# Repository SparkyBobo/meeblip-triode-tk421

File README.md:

# That Time I Promised My Friend a Synth… and Finally Delivered (40 Years Later!)

Let’s rewind to the 1980s—big hair, neon everything, and me, a seventh grader with a wild electronics obsession. Enter my buddy “F” (not his real name, but let’s roll with it—think F Murray Abraham from Amadeus,

because inside jokes are forever). F was the piano prodigy, I was the kid who thought soldering irons were cool, and together we were the ultimate middle school odd couple.

One day, I had a brilliant idea: “Hey F, why don’t you give me a few hundred bucks so I can build you a Moog-style synthesizer from a magazine article?” Because that’s how open-source worked back then—no GitHub, just guts and glue.

F, being the wise soul, realized this was probably a recipe for disaster (and possibly a fire hazard). Instead, F asked for a Roland synth for Christmas. Smart move, right? That was the moment F’s musical journey truly began.

He’s now a fantastic musician, and we rocked out in our high school band, the *Residudes*. F swears my synth hype is what nudged him from classical piano to modern music, so I’ll take partial credit for his rockstar status.

Fast forward: F and I still swap music nerd tidbits. He’s even inspired me to learn music (shoutout to my 70+ day Duolingo streak!). But here’s the kicker—I never actually built that synth. Oops. So, I decided it was time to

make good on my decades-old promise. After some deep dives into my parts bin and the wilds of the internet, I found the perfect open-source project: the [MeeBlip Triode](https://meeblip.com/products/meeblip-triode-synthesizer). It’s affordable, it’s awesome, and it’s my way of finally delivering on that synth promise from the Reagan era.

So here’s to friendship, music, and never letting a 40-year-old promise die. Sometimes, the best things really are worth the wait.

## Build Notes: AKA “How I Frankensteined This Synth Together”

* Parts Bin Olympics: My main goal was to spend as little money as possible on parts, not to be cheap, just to makes this a thing I threw together as much as possible.
* Analog Chip Hunt: Turns out, my stash didn’t have the right analog chips. Had to buy those. Same story for eight matching 10k potentiometers—those got ordered, but I did have a vintage audio taper 10k for volume just chilling in the bin.
* Processor Swap: The original build called for a different processor, but I had an ATMega 644 lying around, so why not? Plus, the DIP-40 package gives it that retro “I built this in the 80s” vibe. I tried to stick to the original circuit and microprocessor connections as much as possible not because I'm afraid of firmware changes, I just thoughts it would be easier.
* Through-Hole Throwback: Most resistors and capacitors are through-hole, because that’s what I had and they look delightfully vintage. Non-electrolytic caps? All from a random kit I bought for experimenting.
* Why use 1 part when 2 will do: Some components ended up with two passives in parallel or series. Why? Because I was determined to use what I had instead of buying new stuff. If you spot C14.1, C14.2, R15.1, or R15.2 looking a little extra, that’s just me flexing my parts bin muscles.
* Surface Mount Sneak-In: A few surface mount parts made it in, mostly to save space and because I had leftovers. Sorry for the modern touch, but hey, it’s all about balance.
* PCB Front Panel Hack: I love using PCBs as front panels—Kicad makes layout a breeze and it’s cheap. This synth is rocking three boards: bottom for the guts, middle for perfect potentiometer height, and the faceplate for that pro finish.
* Oldest Part Award: The power switch is a true relic—I’ve been lugging it around since the late 80s. It's actually an ON-OFF-ON switch but I thought when else am I gonna use it? And what's so bad about having 2 on positions? Runnerup is the resistors: Straight outta my college electronics kit from the late 80s/early 90s.

## Where Credit Is Due

Let’s be real: this project is standing on the shoulders of other. I didn’t just whip up the MeeBlip Triode out of thin air—there’s a whole crew who did the heavy lifting long before I ever busted out my soldering iron. So, here’s a big, sparkly shout-out (because it’s not just what the license says, it’s the right thing to do):

MeeBlip Contributors:

* Jarek Ziembicki: The OG—created the original AVRsynth, which is the backbone of this whole project.
* Laurie Biddulph: Translation superstar! Worked with Jarek to make those comments readable in English and ported the code to Atmega16.
* Daniel Kruszyna: Idea machine—extended AVRsynth and sprinkled in several concepts that MeeBlip now rocks.
* Julian Schmidt: Filter genius—came up with the original Meeblip digital filter algorithm.
* Axel Werner: Code ninja—optimized, squashed bugs, and brought in new bandlimited waveforms.
* James Grahame: Hardware and firmware mastermind behind MeeBlip’s physical and digital awesomeness.
* [MeeBlip Triode on GitHub](https://github.com/MeeBlip/meeblip-triode)

So, if you’re loving this synth saga, send some good vibes to these legends. Without their brainpower, my 40-year-old promise would still be stuck in the parts bin!

Sparky: 

F:

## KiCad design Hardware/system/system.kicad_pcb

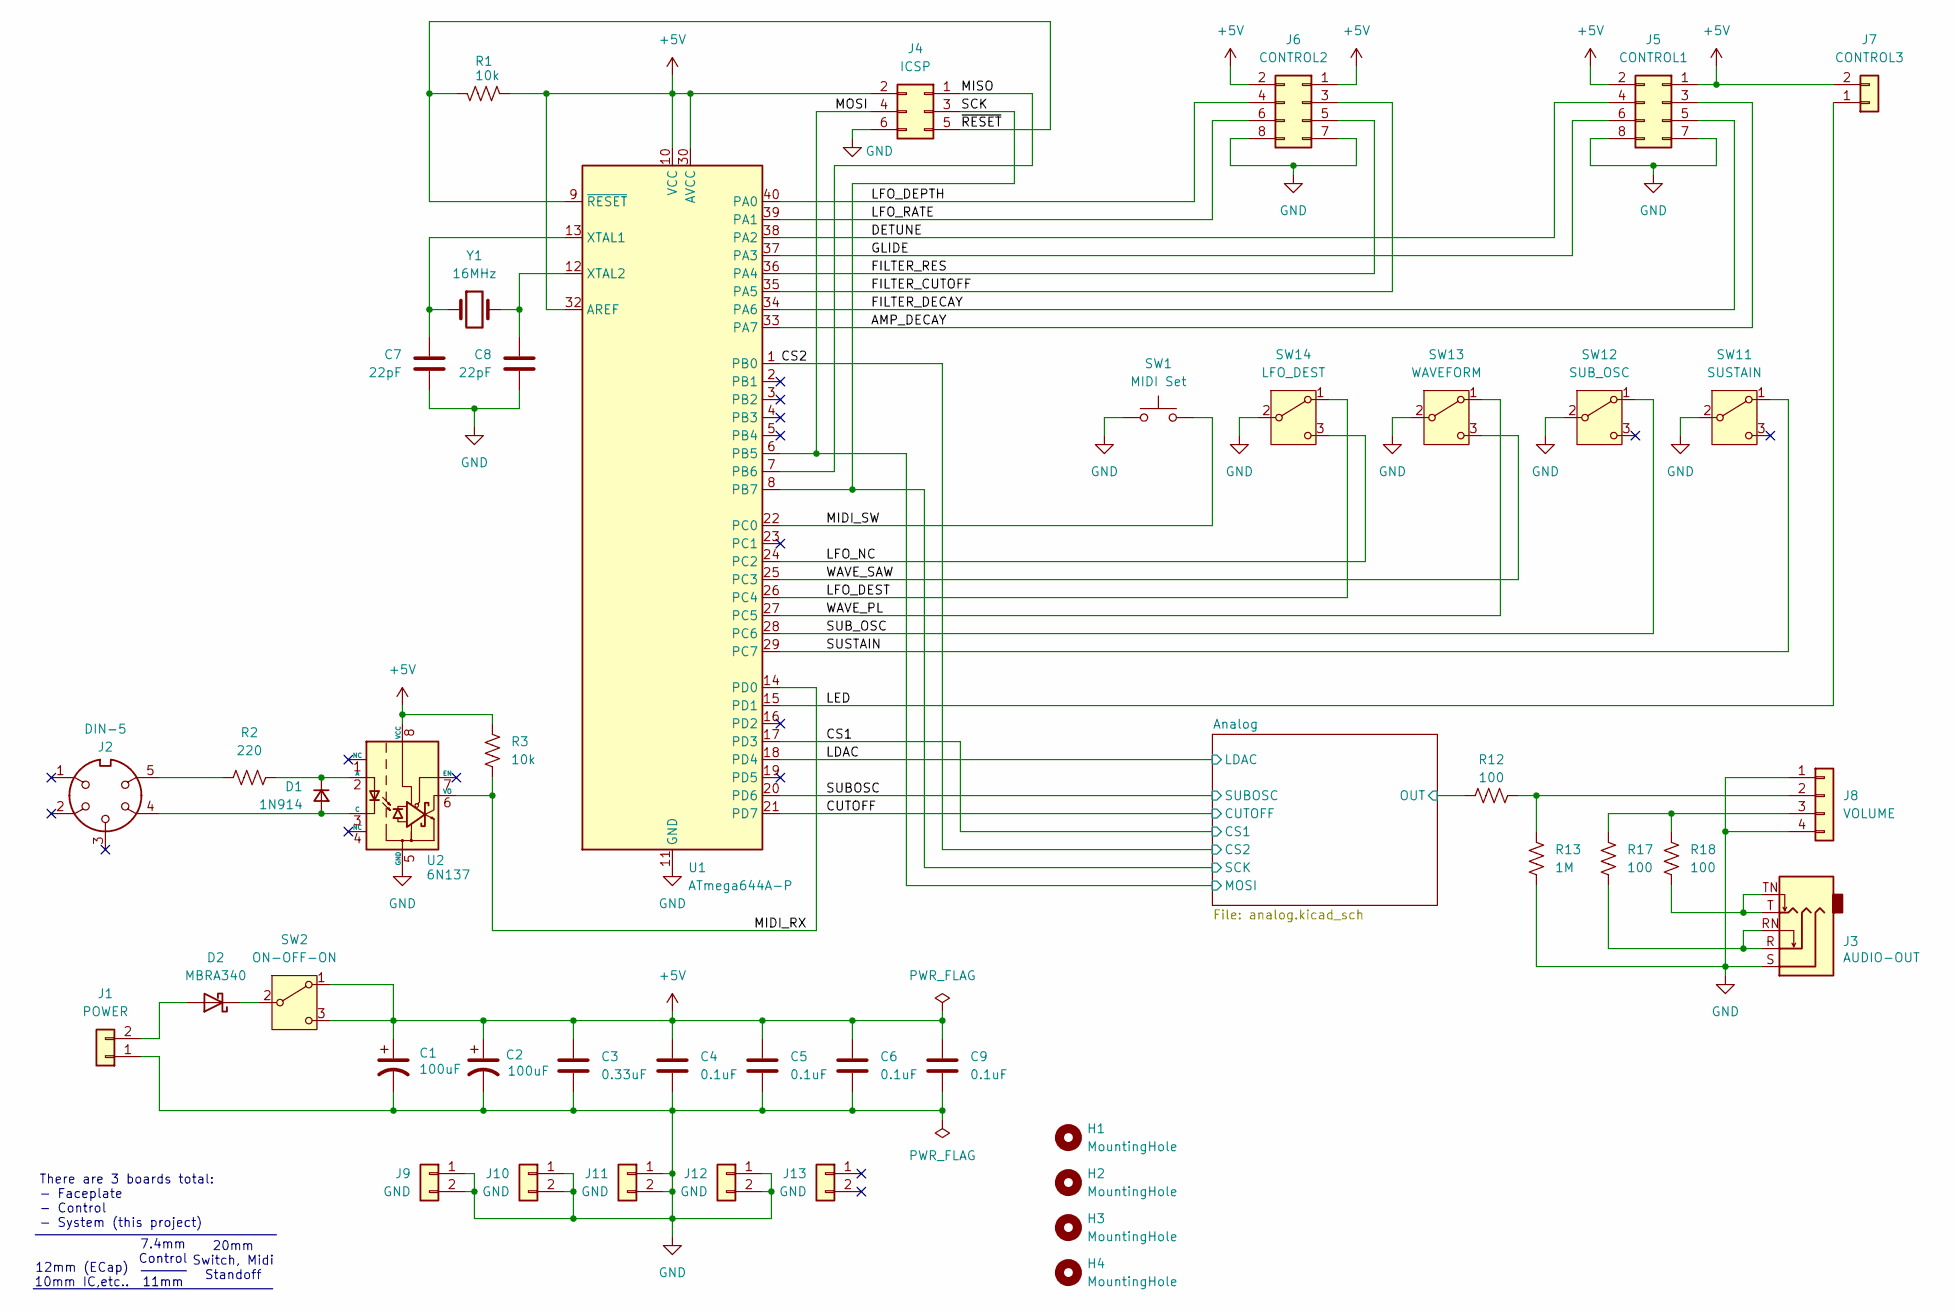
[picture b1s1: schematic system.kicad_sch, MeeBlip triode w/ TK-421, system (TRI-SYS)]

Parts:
C1, C2: 100uF; CP_Radial_D5.0mm_P2.00mm
C3: 0.33uF; C_Rect_L7.2mm_W3.0mm_P5.00mm_FKS2_FKP2_MKS2_MKP2
C4, C5, C6, C9: 0.1uF; C_Rect_L7.2mm_W3.0mm_P5.00mm_FKS2_FKP2_MKS2_MKP2
C7, C8: 22pF; C_Rect_L7.2mm_W3.0mm_P5.00mm_FKS2_FKP2_MKS2_MKP2
D1: 1N914; D_DO-35_SOD27_P10.16mm_Horizontal
D2: MBRA340; D_SMA_Handsoldering
H1, H2, H3, H4: MountingHole; MountingHole_3mm
J1: POWER; PhoenixContact_MC_1,5_2-G-3.81_1x02_P3.81mm_Horizontal
J2: DIN-5; MIDI_DIN_5
J3: AUDIO-OUT; Jack_3.5mm_Adafruit_1699_Horizontal
J4: ICSP; PinHeader_2x03_P2.54mm_Vertical
J5: CONTROL1; PinHeader_2x04_P2.54mm_Vertical
J6: CONTROL2; PinHeader_2x04_P2.54mm_Vertical
J7: CONTROL3; PinHeader_1x02_P2.54mm_Vertical
J8: VOLUME; PinHeader_1x04_P2.54mm_Vertical
J9, J10, J11, J12, J13: GND; PinHeader_1x02_P2.54mm_Vertical
R1: 10k; R_1206_3216Metric_Pad1.30x1.75mm_HandSolder
R2: 220; R_Axial_DIN0207_L6.3mm_D2.5mm_P10.16mm_Horizontal
R3: 10k; R_Axial_DIN0207_L6.3mm_D2.5mm_P10.16mm_Horizontal
R12, R17, R18: 100; R_Axial_DIN0207_L6.3mm_D2.5mm_P10.16mm_Horizontal
R13: 1M; R_Axial_DIN0207_L6.3mm_D2.5mm_P10.16mm_Horizontal
SW1: MIDI Set; SW_PUSH_6mm
SW2: ON-OFF-ON; ESWITCH_100_SPDT_M1_RA
SW11: SUSTAIN; ESWITCH_100_SPDT_M1
SW12: SUB_OSC; ESWITCH_100_SPDT_M1
SW13: WAVEFORM; ESWITCH_100_SPDT_M1
SW14: LFO_DEST; ESWITCH_100_SPDT_M1
U1: ATmega644A-P; DIP-40_W15.24mm
U2: 6N137; DIP-8_W7.62mm
Y1: 16MHz; Crystal_HC49-U_Vertical

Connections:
+5V: C1.1, C2.1, C3.1, C4.1, C5.1, C6.1, C9.1, J4.2, J5.1, J5.2, J6.1, J6.2, J7.2, R1.1, R3.1, SW2.1 (A), SW2.3 (C), U1.10 (VCC), U1.30 (AVCC), U1.32 (AREF), U2.8 (VCC); also elsewhere on the board
/AMP_DECAY: J5.3, U1.33 (PA7)
/Analog/OUT: R12.1; also elsewhere on the board
/CS1: U1.17 (PD3); also elsewhere on the board
/CS2: U1.1 (PB0); also elsewhere on the board
/CUTOFF: U1.21 (PD7); also elsewhere on the board
/DETUNE: J5.4, U1.38 (PA2)
/FILTER_CUTOFF: J6.3, U1.35 (PA5)
/FILTER_DECAY: J5.5, U1.34 (PA6)
/FILTER_RES: J6.5, U1.36 (PA4)
/GLIDE: J5.6, U1.37 (PA3)
/LDAC: U1.18 (PD4); also elsewhere on the board
/LED: J7.1, U1.15 (PD1)
/LFO_DEPTH: J6.4, U1.40 (PA0)
/LFO_DEST: SW14.1 (A), U1.26 (PC4)
/LFO_NC: SW14.3 (C), U1.24 (PC2)
/LFO_RATE: J6.6, U1.39 (PA1)
/MIDI_RX: R3.2, U1.14 (PD0), U2.6 (VO)
/MIDI_SW: SW1.2, U1.22 (PC0)
/MISO: J4.1, U1.7 (PB6)
/MOSI: J4.4, U1.6 (PB5); also elsewhere on the board
/SCK: J4.3, U1.8 (PB7); also elsewhere on the board
/SUBOSC: U1.20 (PD6); also elsewhere on the board
/SUB_OSC: SW12.1 (A), U1.28 (PC6)
/SUSTAIN: SW11.1 (A), U1.29 (PC7)
/WAVE_PL: SW13.1 (A), U1.27 (PC5)
/WAVE_SAW: SW13.3 (C), U1.25 (PC3)
/~RESET: J4.5, R1.2, U1.9 (~RESET)
GND: C1.2, C2.2, C3.2, C4.2, C5.2, C6.2, C7.2, C8.2, C9.2, J1.1, J3.S, J4.6, J5.7, J5.8, J6.7, J6.8, J8.1, J8.4, J9.1, J9.2, J10.1, J10.2, J11.1, J11.2, J12.1, J12.2, R13.2, SW1.1, SW11.2 (B), SW12.2 (B), SW13.2 (B), SW14.2 (B), U1.11 (GND), U1.31 (GND), U2.5 (GND); also elsewhere on the board
unnamed: D1.2 (A), J2.4, U2.3 (C)
unnamed: D1.1 (K), R2.2, U2.2 (A)
unnamed: D2.2 (A), J1.2
unnamed: D2.1 (K), SW2.2 (B)
unnamed: J2.5, R2.1
unnamed: J3.R, J3.RN, R17.2
unnamed: J3.T, J3.TN, R18.2
unnamed: J8.2, R12.2, R13.1
unnamed: J8.3, R17.1, R18.1
unnamed: C7.1, U1.13 (XTAL1), Y1.1
unnamed: C8.1, U1.12 (XTAL2), Y1.2

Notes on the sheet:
There are 3 boards total: - Faceplate - Control - System (this project)
10mm IC,etc..
20mm Switch, Midi Standoff
12mm (ECap)
11mm
7.4mm Control

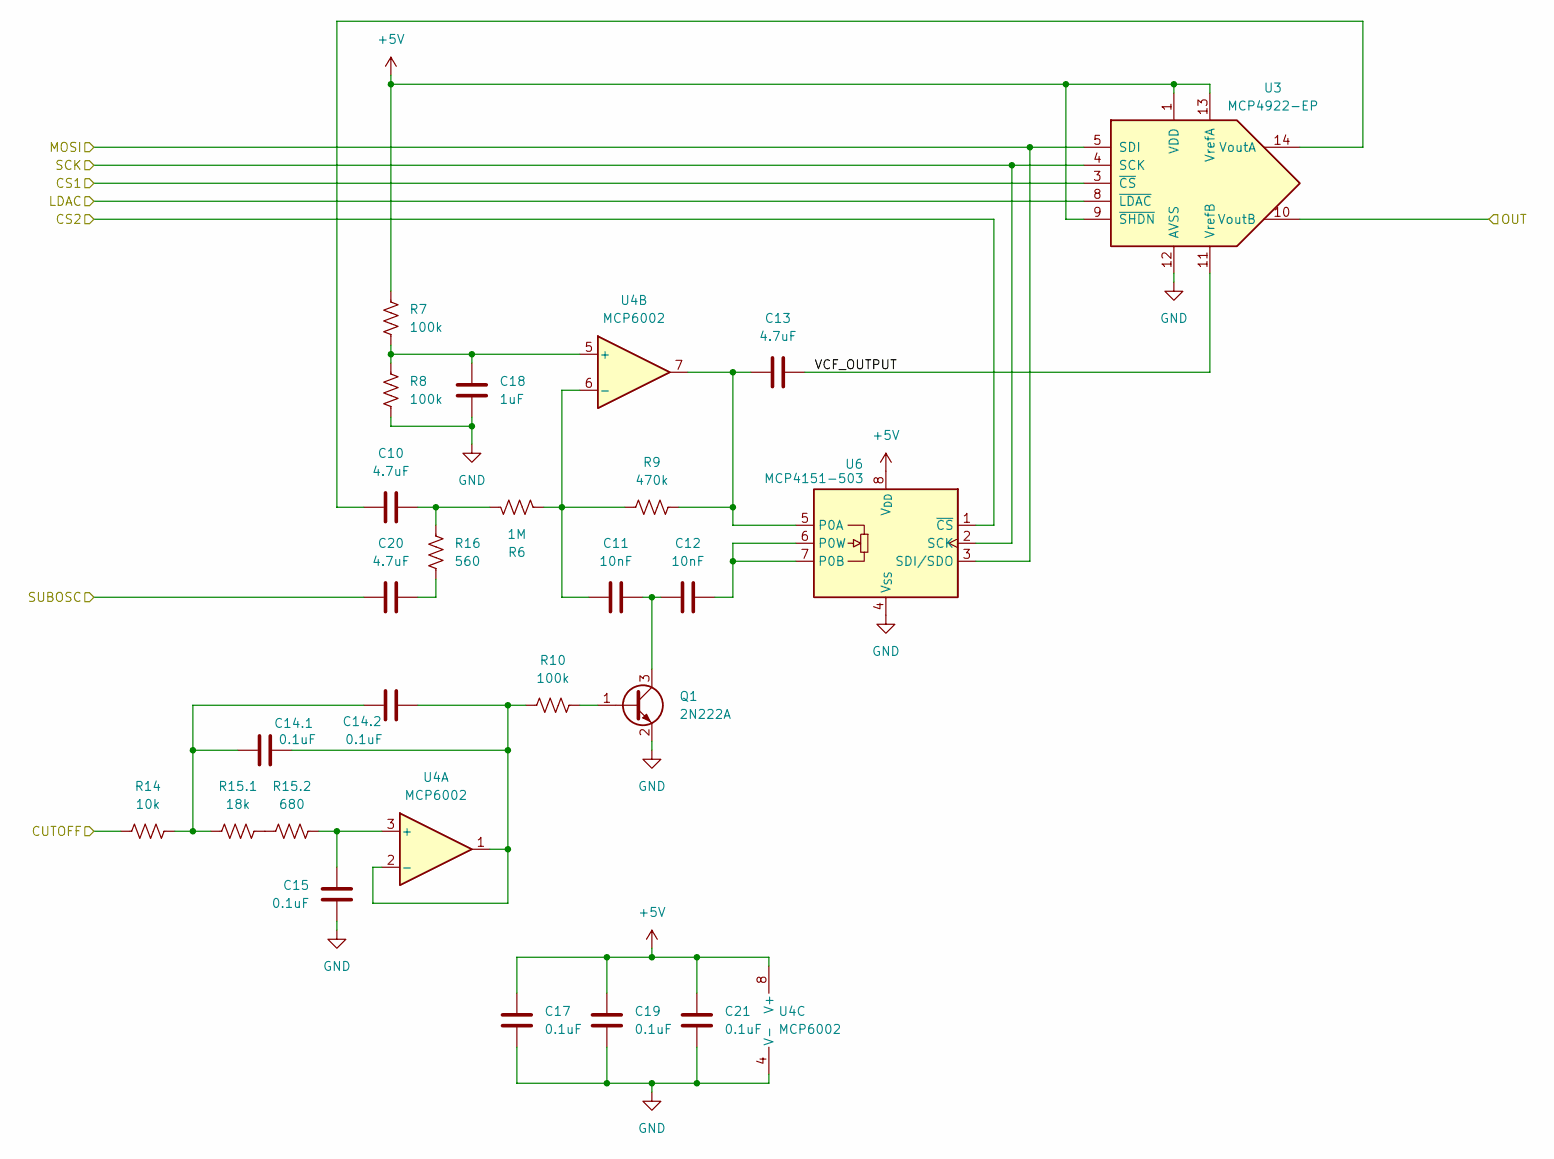
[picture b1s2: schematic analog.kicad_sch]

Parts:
C10, C13, C20: 4.7uF; C_Rect_L7.2mm_W3.0mm_P5.00mm_FKS2_FKP2_MKS2_MKP2
C11, C12: 10nF; C_Rect_L7.2mm_W3.0mm_P5.00mm_FKS2_FKP2_MKS2_MKP2
C14.1, C14.2, C15, C17, C19, C21: 0.1uF; C_Rect_L7.2mm_W3.0mm_P5.00mm_FKS2_FKP2_MKS2_MKP2
C18: 1uF; C_Rect_L7.2mm_W3.0mm_P5.00mm_FKS2_FKP2_MKS2_MKP2
Q1: 2N222A; TO-92_HandSolder
R6: 1M; R_Axial_DIN0207_L6.3mm_D2.5mm_P10.16mm_Horizontal
R7, R8, R10: 100k; R_Axial_DIN0207_L6.3mm_D2.5mm_P10.16mm_Horizontal
R9: 470k; R_Axial_DIN0207_L6.3mm_D2.5mm_P10.16mm_Horizontal
R14: 10k; R_Axial_DIN0207_L6.3mm_D2.5mm_P10.16mm_Horizontal
R15.1: 18k; R_Axial_DIN0207_L6.3mm_D2.5mm_P10.16mm_Horizontal
R15.2: 680; R_Axial_DIN0207_L6.3mm_D2.5mm_P10.16mm_Horizontal
R16: 560; R_Axial_DIN0207_L6.3mm_D2.5mm_P10.16mm_Horizontal
U3: MCP4922-EP; DIP-14_W7.62mm
U4: MCP6002; DIP-8_W7.62mm
U6: MCP4151-503; DIP-8_W7.62mm

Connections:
+5V: C17.1, C19.1, C21.1, R7.1, U3.1 (VDD), U3.9 (~SHDN), U3.13 (VrefA), U4.8 (V+), U6.8 (V_{DD}); also elsewhere on the board
/Analog/OUT: U3.10 (VoutB); also elsewhere on the board
/Analog/VCF_OUTPUT: C13.2, U3.11 (VrefB)
/CS1: U3.3 (~CS); also elsewhere on the board
/CS2: U6.1 (~CS); also elsewhere on the board
/CUTOFF: R14.1; also elsewhere on the board
/LDAC: U3.8 (~LDAC); also elsewhere on the board
/MOSI: U3.5 (SDI), U6.3 (SDI/SDO); also elsewhere on the board
/SCK: U3.4 (SCK), U6.2 (SCK); also elsewhere on the board
/SUBOSC: C20.1; also elsewhere on the board
GND: C15.2, C17.2, C18.2, C19.2, C21.2, Q1.2 (E), R8.2, U3.12 (AVSS), U4.4 (V-), U6.4 (V_{SS}); also elsewhere on the board
unnamed: C10.2, R6.2, R16.1
unnamed: C14.1.1, C14.2.2, R14.2, R15.1.1
unnamed: C20.2, R16.2
unnamed: Q1.1 (B), R10.2
unnamed: C11.2, C12.1, Q1.3 (C)
unnamed: R15.1.2, R15.2.1
unnamed: C10.1, U3.14 (VoutA)
unnamed: C15.1, R15.2.2, U4.3 (+)
unnamed: C14.1.2, C14.2.1, R10.1, U4.1, U4.2 (-)
unnamed: C18.1, R7.2, R8.1, U4.5 (+)
unnamed: C11.1, R6.1, R9.1, U4.6 (-)
unnamed: C13.1, R9.2, U4.7, U6.5 (P0A)
unnamed: C12.2, U6.6 (P0W), U6.7 (P0B)

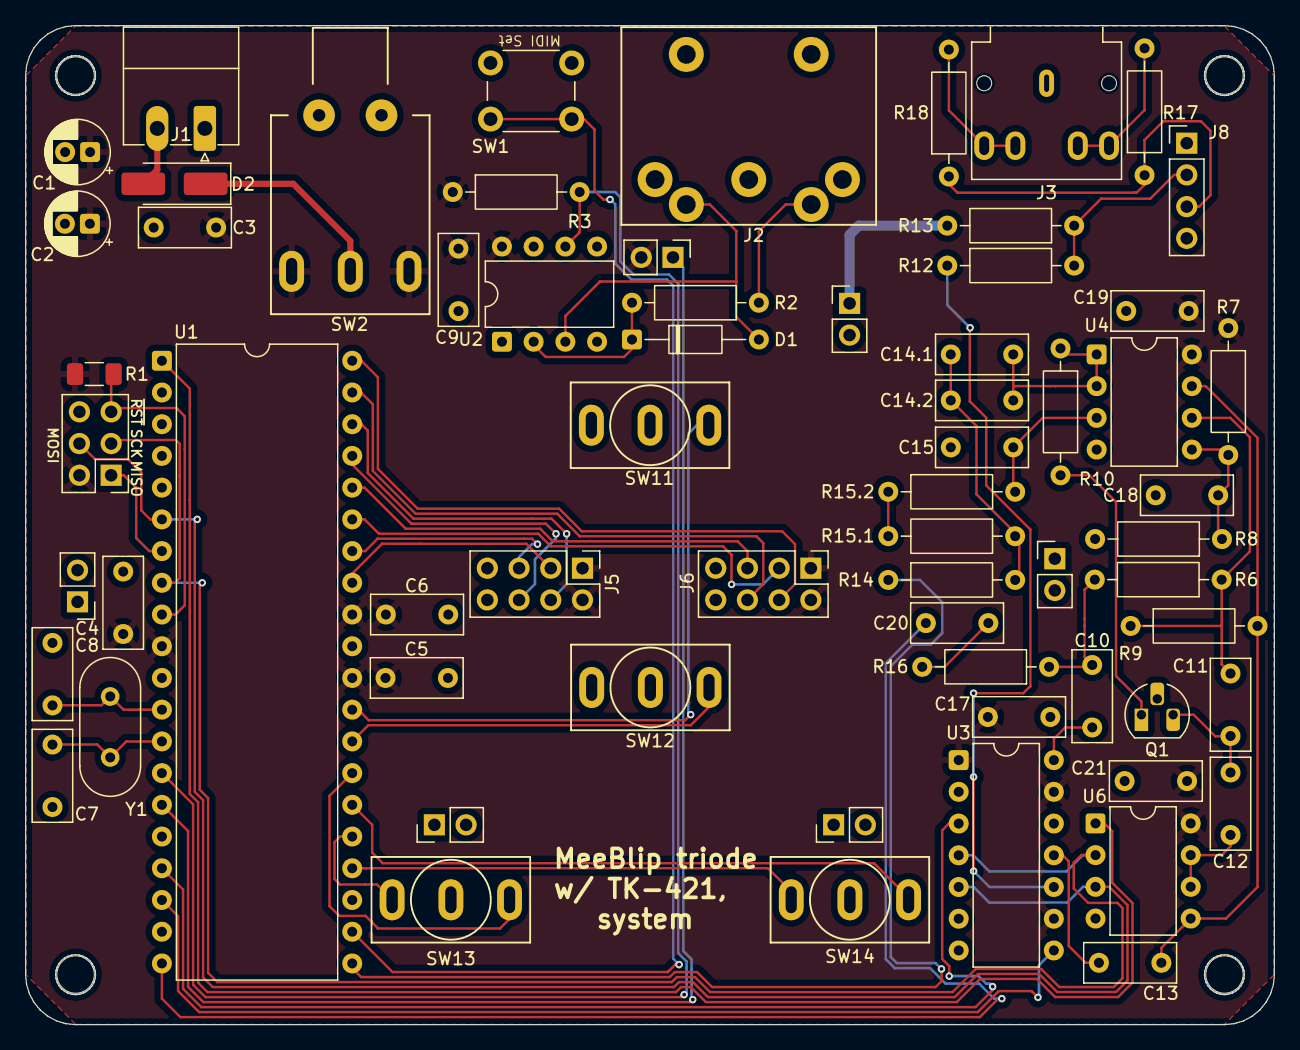
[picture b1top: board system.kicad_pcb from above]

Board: 2 copper layers, 100.0 x 80.0 mm, 69 parts (0 on the bottom side), 54 nets.

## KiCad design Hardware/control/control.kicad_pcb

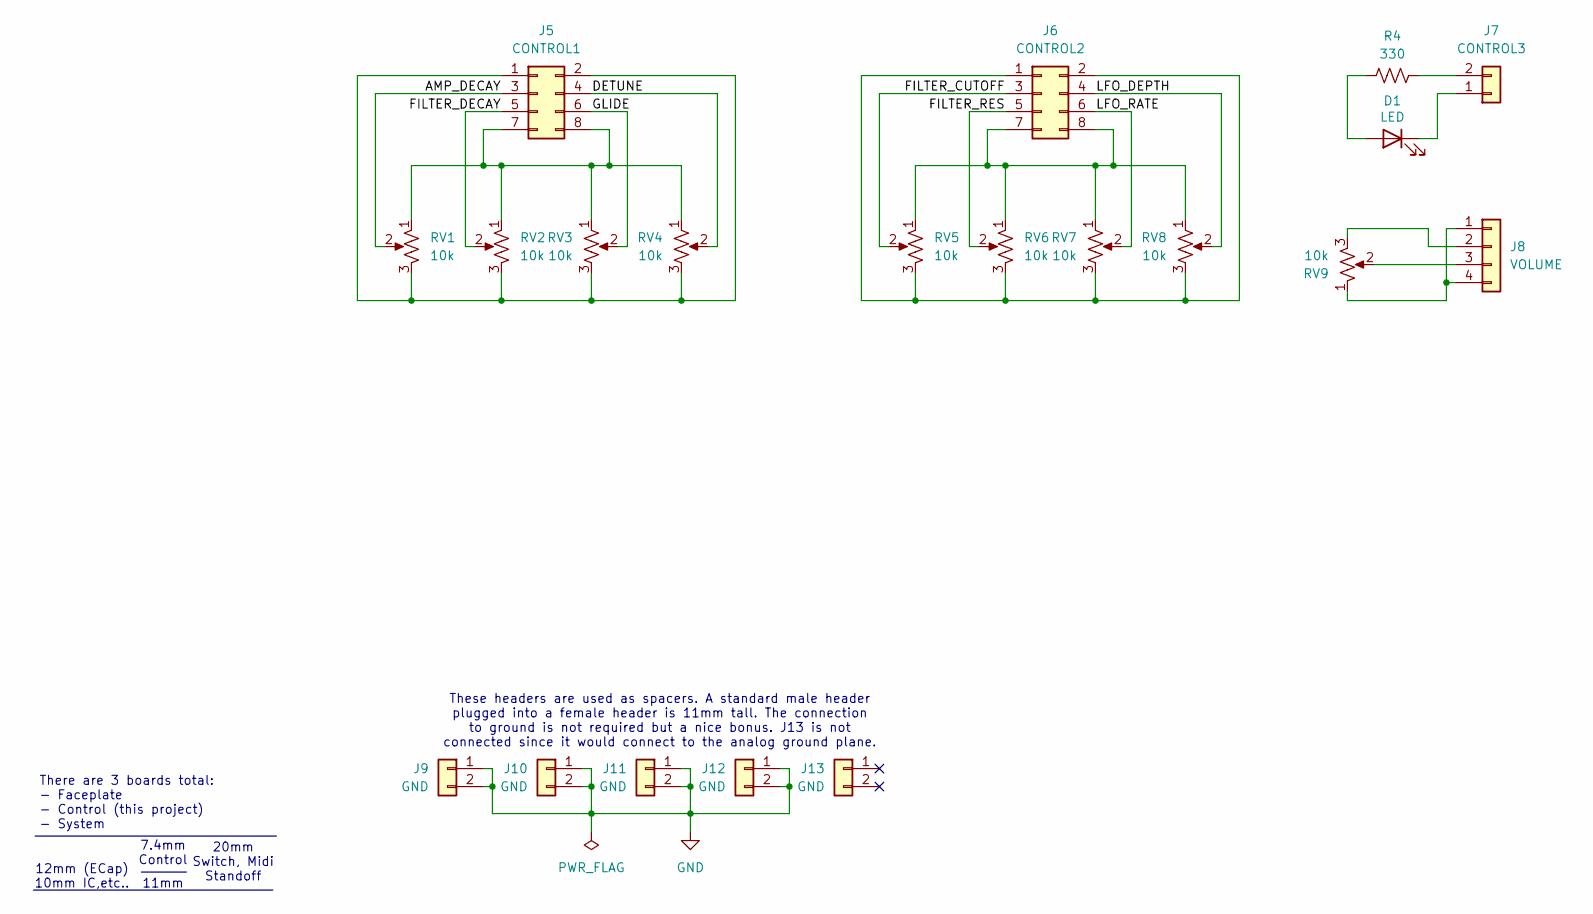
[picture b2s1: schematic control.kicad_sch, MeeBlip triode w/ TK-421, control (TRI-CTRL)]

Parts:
D1: LED; LED_D5.0mm
J5: CONTROL1; PinHeader_2x04_P2.54mm_Vertical
J6: CONTROL2; PinHeader_2x04_P2.54mm_Vertical
J7: CONTROL3; PinHeader_1x02_P2.54mm_Vertical
J8: VOLUME; PinHeader_1x04_P2.54mm_Vertical
J9, J10, J11, J12, J13: GND; PinHeader_1x02_P2.54mm_Vertical
R4: 330; R_Axial_DIN0207_L6.3mm_D2.5mm_P10.16mm_Horizontal
RV1, RV2, RV3, RV4, RV5, RV6, RV7, RV8, RV9: 10k; BOURNS_PTV09A_1

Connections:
/AMP_DECAY: J5.3, RV1.2
/DETUNE: J5.4, RV4.2
/FILTER_CUTOFF: J6.3, RV5.2
/FILTER_DECAY: J5.5, RV2.2
/FILTER_RES: J6.5, RV6.2
/GLIDE: J5.6, RV3.2
/LFO_DEPTH: J6.4, RV8.2
/LFO_RATE: J6.6, RV7.2
GND: J9.1, J9.2, J10.1, J10.2, J11.1, J11.2, J12.1, J12.2
unnamed: D1.2 (A), R4.1
unnamed: D1.1 (K), J7.1
unnamed: J5.1, J5.2, RV1.3, RV2.3, RV3.3, RV4.3
unnamed: J5.7, J5.8, RV1.1, RV2.1, RV3.1, RV4.1
unnamed: J6.1, J6.2, RV5.3, RV6.3, RV7.3, RV8.3
unnamed: J6.7, J6.8, RV5.1, RV6.1, RV7.1, RV8.1
unnamed: J7.2, R4.2
unnamed: J8.1, J8.4, RV9.1
unnamed: J8.2, RV9.3
unnamed: J8.3, RV9.2

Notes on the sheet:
11mm
20mm Switch, Midi Standoff
There are 3 boards total: - Faceplate - Control (this project) - System
12mm (ECap)
10mm IC,etc..
7.4mm Control
These headers are used as spacers. A standard male header plugged into a female header is 11mm tall. The connection to ground is not required but a nice bonus. J13 is not connected since it would connect to the analog ground plane.

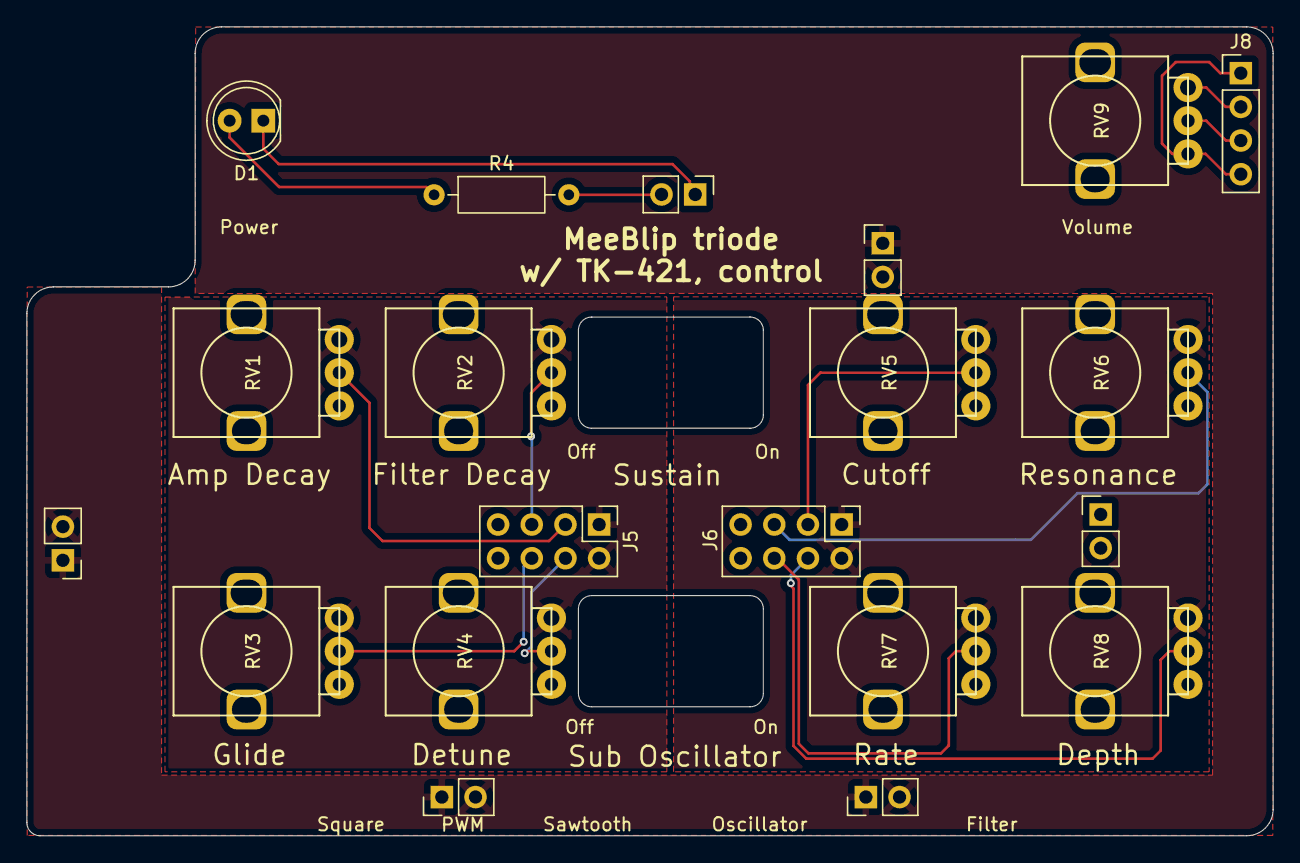
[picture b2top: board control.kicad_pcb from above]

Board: 2 copper layers, 94.0 x 61.0 mm, 20 parts (0 on the bottom side), 19 nets.

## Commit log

2026-01-01 Initial commit - Forked from original project - Redrawn in Kicad 9.x - Board layout to accomodate my parts bin
2026-01-02 Update the readme.
2026-01-02 Add pics from 1983.
2026-01-02 Format as images. Delete old readme.

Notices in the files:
Hardware/control/control.kicad_pcb:
https://creativecommons.org/licenses/by-sa/4.0
Released under the Creative Commons Attribution Share-Alike 4.0 License
